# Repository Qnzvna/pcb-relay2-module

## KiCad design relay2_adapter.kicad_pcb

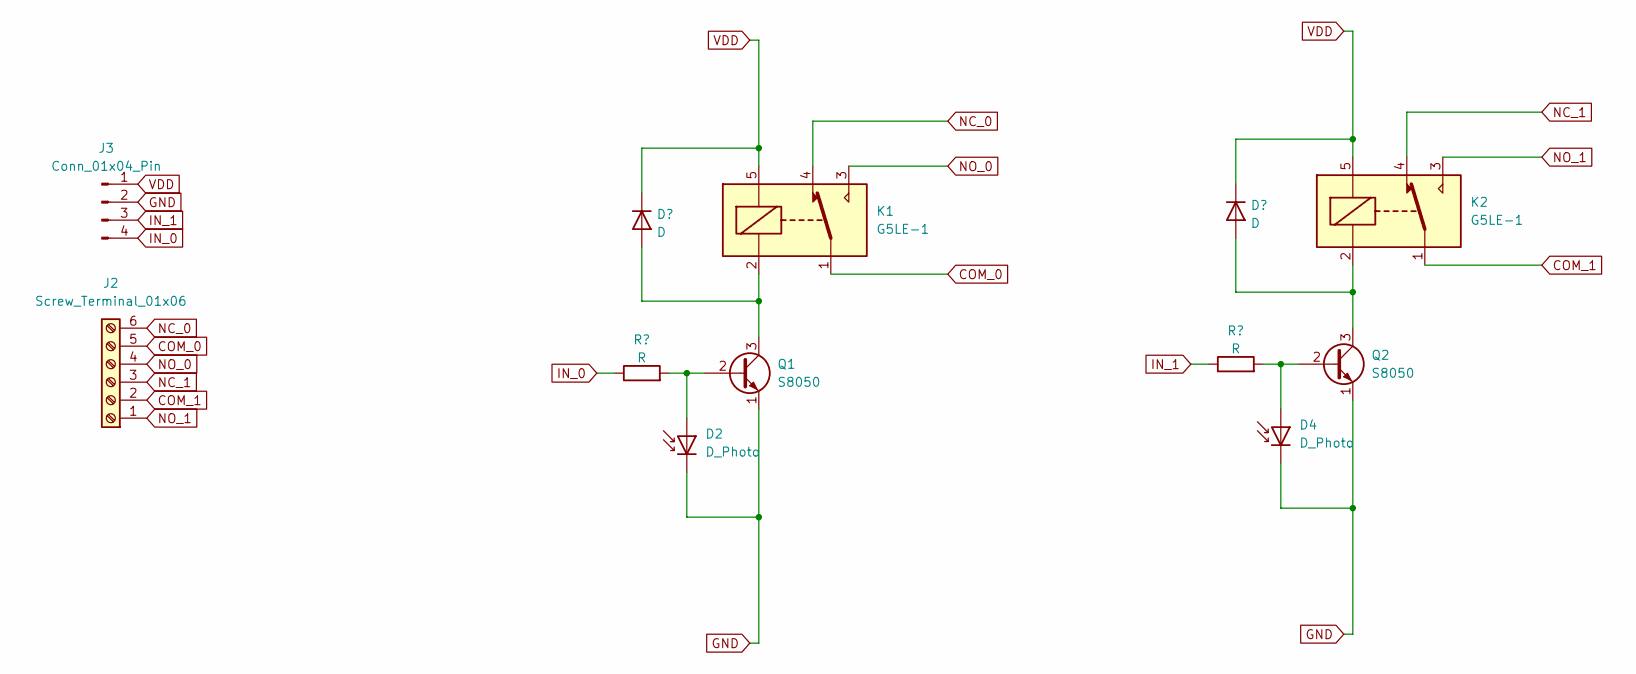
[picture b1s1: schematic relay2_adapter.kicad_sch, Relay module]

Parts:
D1, D3: D; D_DO-35_SOD27_P7.62mm_Horizontal
D2, D4: D_Photo; LED_D4.0mm
J2: Screw_Terminal_01x06; TerminalBlock_Phoenix_PT-1,5-6-5.0-H_1x06_P5.00mm_Horizontal
J3: Conn_01x04_Pin; PinHeader_1x04_P2.54mm_Vertical
K1, K2: G5LE-1; Relay_SPDT_Omron-G5LE-1
Q1, Q2: S8050; TO-92_Inline
R1, R2: R; R_1206_3216Metric_Pad1.30x1.75mm_HandSolder

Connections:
COM_0: J2.5, K1.1
COM_1: J2.2, K2.1
GND: D2.1 (K), D4.1 (K), J3.2, Q1.1 (E), Q2.1 (E)
IN_0: J3.4, R1.1
IN_1: J3.3, R2.1
NC_0: J2.6, K1.4
NC_1: J2.3, K2.4
NO_0: J2.4, K1.3
NO_1: J2.1, K2.3
unnamed: D1.2 (A), K1.2, Q1.3 (C)
unnamed: D2.2 (A), Q1.2 (B), R1.2
unnamed: D3.2 (A), K2.2, Q2.3 (C)
unnamed: D4.2 (A), Q2.2 (B), R2.2
VDD: D1.1 (K), D3.1 (K), J3.1, K1.5, K2.5

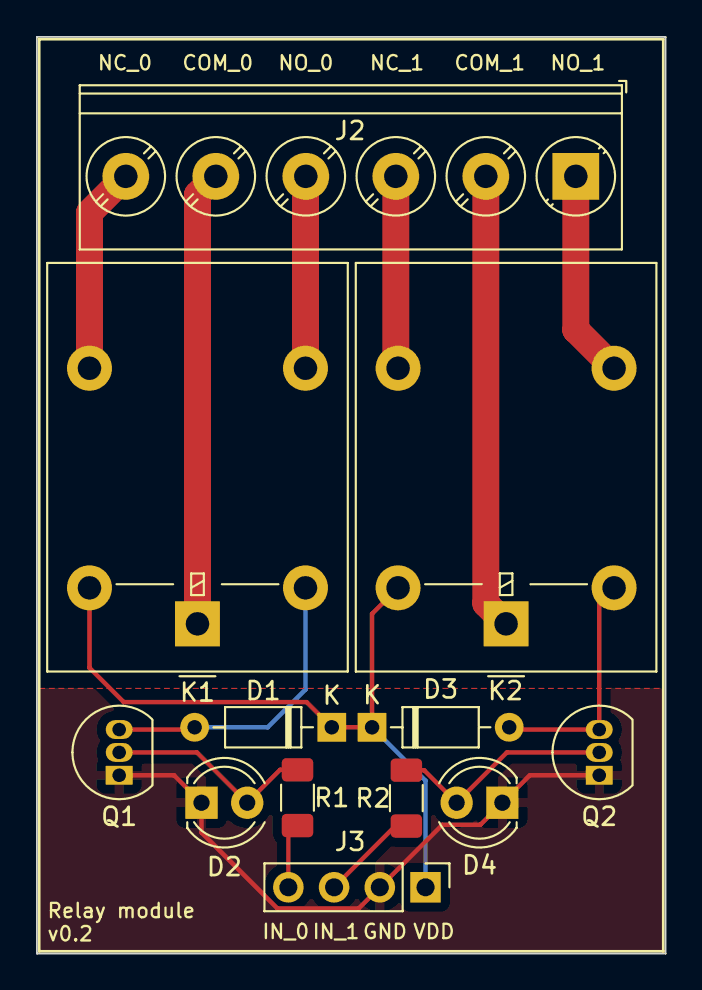
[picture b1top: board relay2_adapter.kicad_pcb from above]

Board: 2 copper layers, 34.9 x 50.9 mm, 12 parts (0 on the bottom side), 14 nets.

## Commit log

2023-06-30 Relay module for 2 v0.2
